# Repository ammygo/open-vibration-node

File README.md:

# Open Vibration Node

An open hardware and open firmware vibration sensing node for industrial condition
monitoring — analysing vibration **on the device** and reporting results over LoRaWAN to a
gateway you run yourself, with no mandatory cloud service.

> **Status: sensor board verified, radio path not yet exercised.** The second-generation
> sensor board has been manufactured and verified on the bench — the sensor identifies
> correctly, gravity and impact-response tests pass, and the noise floor sits at ~18 mg RMS
> across the full 6.3 kHz bandwidth on a bench ([measurements](docs/measurements.md)). The RAK3112 module has so far served only as the
> host MCU for those tests; the SX1262 radio has not yet been brought up. Mechanical
> integration and the signal-processing firmware are the current work.

*The two 28 mm boards that make up a node — sensor board and radio board, both sides.
More photographs: [docs/images](docs/images/).*

## Why this project exists

Predictive maintenance works: measuring vibration on motors, bearings, pumps and fans
reveals developing faults weeks or months before they cause a breakdown. The techniques
are well documented in engineering literature, and the sensors cost a few euros.

Access to them is not open, though. Commercial condition-monitoring systems are closed
end to end — proprietary sensors, proprietary gateways, and a vendor cloud that must stay
reachable and paid for, or the equipment stops being monitored. Prices start in the
hundreds of euros per measurement point, which puts continuous monitoring out of reach for
small manufacturers, municipal utilities, water pumping stations and building services —
exactly the operators who can least afford an unplanned failure.

Open vibration-monitoring projects do exist. The ones I have found stop at a development
board on a desk, depend on a vendor cloud, or use accelerometers limited to a few hundred
hertz — which rules out the 1–6 kHz region where bearing faults first appear. What is
missing is a node that combines the bandwidth needed for real diagnostics with local-first
operation and documentation good enough to rebuild it. This project aims to be that node.

## How this compares with existing work

| Approach | Usable bandwidth | Power / connectivity | Openness |
|---|---|---|---|
| Commercial condition-monitoring systems | Full (piezo-based) | Battery or wired; vendor cloud mandatory | Closed end to end; per-point pricing plus subscription |
| Open builds on consumer MEMS (ADXL345 / LIS3DH class) | ~200–800 Hz | Battery; various | Open, but physically blind to the 1–6 kHz bearing-fault region |
| Wired piezo + DAQ setups | Full | Mains power and cabling per point | Mixed; cabling dominates per-point cost |
| **This project** | **DC–6.3 kHz (IIS3DWB)** | **Battery + LoRa; local-first, no mandatory cloud** | **Open: hardware, firmware, docs, production files** |

Open lab-instrument projects — open microscopes, open test equipment — have already shown
that *laboratory-grade but open and rebuildable* is a workable model. This project applies
that model to industrial vibration monitoring.

## Design goals

These are the goals the design is being built towards, not a description of what already
works — see the status above.

- **Analysis on the device.** FFT and envelope processing run on the node's MCU. Only
  results leave the device — a compact payload of dominant frequencies, amplitudes, RMS
  and temperature (target: under 24 bytes), not raw waveforms. This is what makes
  battery-powered operation over a low-bandwidth radio possible at all.
- **Local-first.** LoRaWAN with a self-hosted [ChirpStack](https://www.chirpstack.io/)
  network server: the reference gateway is a Raspberry Pi 5 with an SX1302 eight-channel
  concentrator, and everything from radio to database runs on hardware the operator owns.
  No account, no vendor cloud, no remote kill switch. Cloud services are optional, never
  required.
- **Auditable and reproducible.** Schematics, bill of materials, firmware source and
  enclosure models under free licences, with build documentation detailed enough to
  reproduce a working node.
- **Long field life.** Multi-year operation on a primary lithium cell. Sealed enclosure
  for industrial and outdoor use.
- **Secure by design.** Per-device keys, signed firmware updates and a published software
  bill of materials, so that nodes remain maintainable under the EU Cyber Resilience Act
  rather than becoming unsupported hardware.

## Hardware

| Block | Part | Key figures |
|---|---|---|
| Accelerometer | STMicroelectronics **IIS3DWB** | DC–6.3 kHz flat bandwidth, 26.667 kHz ODR, 75 µg/√Hz noise density, ±2/4/8/16 g, SPI, −40…+105 °C, integrated temperature sensor |
| MCU + radio | RAK Wireless **RAK3112** | ESP32-S3 + Semtech SX1262 in one certified module (LoRa 868 MHz, WiFi, BLE), 23×15 mm |
| Power | Diodes **AP2112K-3.3** LDO | 600 mA, SOT-23-5 (LCSC C51118) |

### Why these parts

**IIS3DWB.** Bearing and mechanical fault signatures live in the 1–6 kHz region, while
ordinary MEMS accelerometers (ADXL345, LIS3DH and similar) are limited to 200–800 Hz —
they physically cannot see what matters. The IIS3DWB gives a flat 6.3 kHz bandwidth at
75 µg/√Hz noise in a single 2.5 × 3.0 mm package, so diagnostics that previously required
a piezoelectric accelerometer with an external conditioner now fit in a 28 mm node running
from a battery.

**RAK3112.** The ESP32-S3 has enough compute to run the FFT locally, which is the whole
premise of the design: the node transmits a spectral summary rather than raw waveforms,
which is what makes both the battery budget and the LoRa duty cycle work. Combining it
with the SX1262 in one certified module means a single component instead of MCU plus radio
plus RF matching, and no antenna network to design. The trade-off is board area in
exchange for reproducibility and a simpler certification path — a deliberate choice for a
project that others are meant to be able to rebuild.

*Everything that goes into one node: the two boards, primary cell, energy buffer,
antennas, printed housing and the aluminium mounting pad.*

### Board architecture

Two 28 mm round boards with the battery between them, joined by seven wires:

- **Sensor board** — IIS3DWB on the bottom layer, facing the measured surface, with
  decoupling capacitors and a CS pull-up.
- **Radio board** — RAK3112 on the top layer (antenna facing away from metal), LDO and
  power components underneath.

Inter-board signals: `GND`, `3V3`, `SPI_CS`, `SPI_SCK`, `SPI_MISO`, `SPI_MOSI`, `INT1`.
Pad order is identical on both boards, so the wires run straight across without crossing.

Placing the accelerometer on the bottom layer is deliberate — it shortens the mechanical
path between the measured surface and the sensing element, which matters far more for
signal fidelity than any amount of filtering afterwards.

### Two data paths

A node normally sends only a spectral summary — a payload of a couple of dozen bytes,
which is what makes years of battery life on a low-bandwidth radio possible at all. That
summary is enough to trend a machine's condition, but not to investigate a fault in detail.

So the node keeps a second path. The RAK3112 carries 8 MB of PSRAM, enough to hold about
50 seconds of the full 26.667 kHz three-axis stream. When something in the trend needs
looking at, an engineer standing next to the machine can trigger a capture and pull the
raw recording off over WiFi, straight to a laptop — no cloud and no gateway involved.
This path works on the bench as of September 2026: a downlink command makes the node record
32768 samples per axis (1.23 s — the PSRAM allows about 50 s; 1.23 s is the current capture
length) from the sensor FIFO into PSRAM and post them over WiFi to the collector (the local
server described above; a laptop also works), which it locates by mDNS.

This is deliberately **on demand** rather than continuous: streaming raw data would end the
battery budget within days. Routine monitoring stays cheap; full detail is available when
it is actually needed.

## Repository layout

| Path | Contents |
|---|---|
| `firmware/tests/` | Bench verification sketches — sensor identification and acquisition |
| `firmware/bench-node/` | Interim point-to-point LoRa node and bench receiver — FIFO acquisition, ISO 10816 velocity RMS, health reporting, raw capture over WiFi |
| `docs/` | Measurements, payload specification draft, build notes |
| `enclosure/` | Mounting pad and housing — CAD sources with open-format exports |
| `tools/` | Design-check utilities: a mirrored-footprint checker and the velocity-RMS filter validation script |
| `hardware/` | KiCad boards plus gerbers, BOM and pick-and-place files for both boards |

## Licences

- Firmware and software: [MIT](LICENSE)
- Hardware design files: CERN-OHL-W-2.0 (see `hardware/LICENSE.txt`)
- Documentation: CC-BY-SA-4.0

## Roadmap

Timing is indicative and assumes part-time development; with project funding it compresses.

1. ~~Sensor board validated on hardware~~ — done, August 2026 ([measurements](docs/measurements.md))
2. ~~Radio bring-up: SX1262 transmit and receive path~~ — done, September 2026: point-to-point
   LoRa link (869.525 MHz, SF7) in both directions, downlink-configurable cadence within the
   duty-cycle budget, on-demand raw capture over WiFi; velocity RMS in the ISO 10816 band
   validated ([measurements](docs/measurements.md#velocity-rms-in-the-iso-10816-band-added-2-september-2026)).
   The interim link terminates in a USB LoRa receiver on the collector (the local server
   described under *Local-first*); roadmap item 4 replaces it with the SX1302 LoRaWAN gateway
   and ChirpStack.
3. Mechanical integration: sensor coupling, sealing, field-ready housing (pad and housing
   models [published](enclosure/); sealing details in progress) — winter 2026/27
4. On-device FFT and envelope processing, LoRaWAN uplink with a versioned payload format
   ([draft specification](docs/payload-spec.md)) — spring 2027. *Interim: FFT, envelope and
   waterfall spectra are computed on the collector from FIFO captures; each packet already
   carries band-limited velocity RMS, crest factor and a sensor-health flag
   ([status](docs/payload-spec.md#bench-protocol-status-2-september-2026)).*
5. Characterisation against a reference accelerometer on a shaker — spring/summer 2027
6. Field deployment on real rotating equipment, with published measurement data — second
   half of 2027
7. Documented reproducible build — someone else assembles a node from this repository —
   late 2027

## About

Built by Laurynas Misiūnas, an electronics engineer in Klaipėda district, Lithuania, with
six years of industrial experience deploying edge AI vision systems and embedded
controllers on production lines. Developed with the support of the Klaipėda Science and
Technology Park (KMTP) innovation support programme.

Contributions, review and questions are welcome — see [CONTRIBUTING.md](CONTRIBUTING.md) or open an issue.

## Transparency: use of generative AI

Engineering decisions, architecture and project direction in this repository are made by
the author. Documentation and English-language texts are drafted with the assistance of a
large language model (Anthropic Claude) and reviewed, corrected and approved by the author
before publication. Commits with LLM-assisted content carry a `Co-Authored-By: Claude`
trailer. Details in [TRANSPARENCY.md](TRANSPARENCY.md).

No firmware, hardware design files or measurement data will be presented as project
deliverables without human authorship and verification.

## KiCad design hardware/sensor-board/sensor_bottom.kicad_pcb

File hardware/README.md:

# Hardware

Two 28 mm round boards, joined by seven wires with the battery between them.

Licence: CERN-OHL-W-2.0 — see [LICENSE.txt](LICENSE.txt).

| Path | Board | Contents |
|---|---|---|
| `sensor-board/` | IIS3DWB accelerometer, bottom layer | KiCad board, gerbers, BOM, pick-and-place |
| `radio-board/` | RAK3112 module (ESP32-S3 + SX1262), LDO | KiCad board, gerbers, BOM, CPL, pick-and-place |

The `production/` files under each board are the sets actually sent for fabrication and
assembly — not idealised exports. Boards from these files have been manufactured and the
sensor board verified on the bench ([measurements](../docs/measurements.md)).

### What the KiCad sources are and are not

**The gerbers are the authoritative artifact** — they are what was manufactured. The KiCad
files are the design sources behind them, and on both boards they differ from the gerbers
in ways worth knowing before you rebuild:

- **Sensor board** — fully routed, but one CS track and its via sit about 0.1 mm from
  where the manufactured gerbers place them. The final clearance fix was applied in the
  export tool rather than back-annotated to KiCad. Electrically identical; regenerating
  gerbers from KiCad will not produce a byte-identical set.
- **Radio board** — carries **placement and netlist only, with no routing**. The routing
  was done in the export tool and exists solely in the gerbers. Opening this file will
  show an unrouted board; that is the actual state of the source, not a damaged file.

If you intend to modify either design, start from the gerbers for what was built and treat
the KiCad files as the placement reference.

*Sensor board (bottom row) and radio board (top row), both sides. The accelerometer sits
on the underside of the sensor board; the RAK3112 module on the top of the radio board.*

## Inter-board wiring

`GND`, `3V3`, `SPI_CS`, `SPI_SCK`, `SPI_MISO`, `SPI_MOSI`, `INT1`.

Pad order is identical on both boards, so the wires run straight across without crossing.

## Layout constraints worth knowing

Two requirements pull against each other on a 28 mm board, and the layout is the
compromise between them:

- The accelerometer needs a **short, stiff mechanical path** to the mounting surface,
  which is why it sits on the bottom layer facing the measured surface rather than on top.
- The radio needs a **clean ground plane and antenna keep-out**, which is why the module
  sits on the top layer with the antenna facing away from the mounted metal.

Splitting these onto two boards resolves the conflict; the cost is the seven-wire harness
and the assembly step that goes with it.

## Before you reorder these boards

Run [`../tools/check_handedness.py`](../tools/README.md) against the sensor board. A
mirrored bottom-layer footprint passes design rule checking and fabricator review and
still cannot be assembled — that mistake cost three revisions here.

## Bill of materials

The BOM files carry LCSC part numbers where the boards were assembled with them, so the
component selection can be reproduced directly. Prices, suppliers and order references are
deliberately not included.

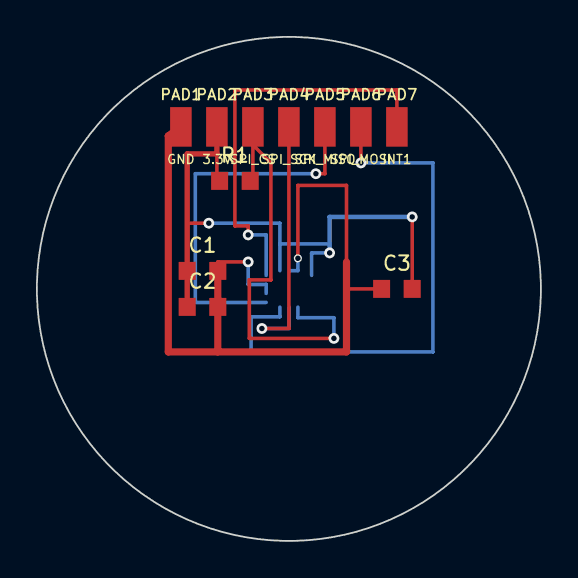
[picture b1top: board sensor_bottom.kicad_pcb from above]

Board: 2 copper layers, 28.0 x 28.0 mm, 12 parts (1 on the bottom side), 7 nets.

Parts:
C1, C3: 100nF; C_0603_1608Metric
C2: 1uF; C_0603_1608Metric
PAD1: GND; PinHeader_1x01_P2.00mm_Vertical
PAD2: 3.3V; PinHeader_1x01_P2.00mm_Vertical
PAD3: SPI_CS; PinHeader_1x01_P2.00mm_Vertical
PAD4: SPI_SCK; PinHeader_1x01_P2.00mm_Vertical
PAD5: SPI_MISO; PinHeader_1x01_P2.00mm_Vertical
PAD6: SPI_MOSI; PinHeader_1x01_P2.00mm_Vertical
PAD7: INT1; PinHeader_1x01_P2.00mm_Vertical
R1: 10k; R_0603_1608Metric
U1: IIS3DWB; LGA-14_3x2.5mm_P0.5mm

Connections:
3.3V: C1.1, C2.1, C3.2, PAD2.2, R1.1, U1.5, U1.8
GND: C1.2, C2.2, C3.1, PAD1.1, U1.2, U1.3, U1.6, U1.7
INT1: PAD7.7, U1.4
SPI_CS: PAD3.3, R1.2, U1.12
SPI_MISO: PAD5.5, U1.1
SPI_MOSI: PAD6.6, U1.14
SPI_SCK: PAD4.4, U1.13

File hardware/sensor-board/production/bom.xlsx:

No. | Quantity | Comment | Designator | Footprint | Value | Manufacturer Part | Manufacturer | Supplier Part | Supplier
1 | 2 | 100nF | C1,C3 | Capacitor_SMD:C_0603_1608Metric
2 | 1 | 1uF | C2 | Capacitor_SMD:C_0603_1608Metric
3 | 1 | GND | PAD1 | Connector_PinHeader_2.00mm:PinHeader_1x01_P2.00mm_Vertical
4 | 1 | 3.3V | PAD2 | Connector_PinHeader_2.00mm:PinHeader_1x01_P2.00mm_Vertical
5 | 1 | SPI_CS | PAD3 | Connector_PinHeader_2.00mm:PinHeader_1x01_P2.00mm_Vertical
6 | 1 | SPI_SCK | PAD4 | Connector_PinHeader_2.00mm:PinHeader_1x01_P2.00mm_Vertical
7 | 1 | SPI_MISO | PAD5 | Connector_PinHeader_2.00mm:PinHeader_1x01_P2.00mm_Vertical
8 | 1 | SPI_MOSI | PAD6 | Connector_PinHeader_2.00mm:PinHeader_1x01_P2.00mm_Vertical
9 | 1 | INT1 | PAD7 | Connector_PinHeader_2.00mm:PinHeader_1x01_P2.00mm_Vertical
10 | 1 | 10k | R1 | Resistor_SMD:R_0603_1608Metric
11 | 1 | IIS3DWB | U1 | Package_LGA:LGA-14_3x2.5mm_P0.5mm

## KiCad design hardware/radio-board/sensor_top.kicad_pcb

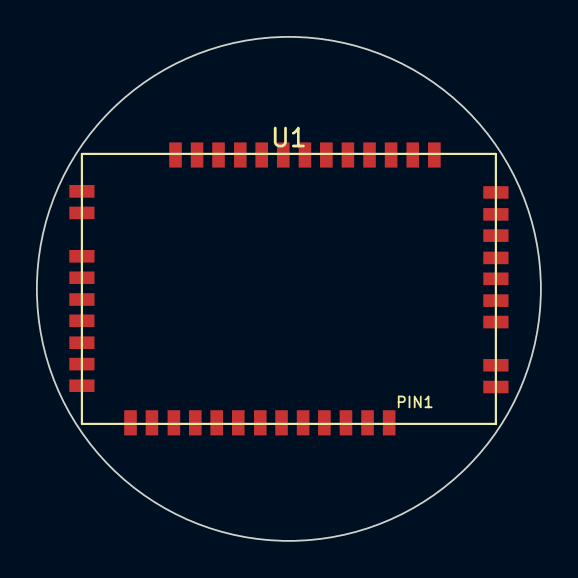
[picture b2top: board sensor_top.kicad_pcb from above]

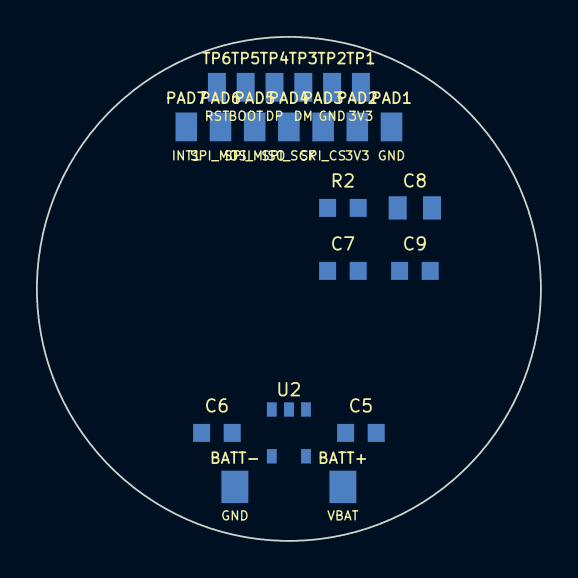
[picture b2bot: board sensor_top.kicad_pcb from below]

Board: 2 copper layers, 28.0 x 28.0 mm, 23 parts (22 on the bottom side), 12 nets, no tracks yet.

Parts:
BATT+: VBAT; PinHeader_1x01_P2.54mm_Vertical
BATT-: GND; PinHeader_1x01_P2.54mm_Vertical
C5, C6, C7: 1uF; C_0603_1608Metric
C8: 10uF; C_0805_2012Metric
C9: 100nF; C_0603_1608Metric
PAD1: GND; PinHeader_1x01_P2.00mm_Vertical
PAD2: 3V3; PinHeader_1x01_P2.00mm_Vertical
PAD3: SPI_CS; PinHeader_1x01_P2.00mm_Vertical
PAD4: SPI_SCK; PinHeader_1x01_P2.00mm_Vertical
PAD5: SPI_MISO; PinHeader_1x01_P2.00mm_Vertical
PAD6: SPI_MOSI; PinHeader_1x01_P2.00mm_Vertical
PAD7: INT1; PinHeader_1x01_P2.00mm_Vertical
R2: 10k; R_0603_1608Metric
TP1: 3V3; PinHeader_1x01_P2.00mm_Vertical
TP2: GND; PinHeader_1x01_P2.00mm_Vertical
TP3: DM; PinHeader_1x01_P2.00mm_Vertical
TP4: DP; PinHeader_1x01_P2.00mm_Vertical
TP5: BOOT; PinHeader_1x01_P2.00mm_Vertical
TP6: RST; PinHeader_1x01_P2.00mm_Vertical
U1: RAK3112
U2: AP2112K-3.3; SOT-23-5

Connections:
3V3: C6.1, C8.1, C9.1, PAD2.1, R2.1, TP1.1, U1.20, U1.21, U2.5
BOOT: TP5.1, U1.24
GND: BATT-.1, C5.2, C6.2, C7.2, C8.2, C9.2, PAD1.1, TP2.1, U1.14, U1.16, U1.22, U1.35, U1.36, U1.38, U1.42, U2.2
INT1: PAD7.1, U1.34
RESET: C7.1, R2.2, TP6.1, U1.17
SPI_CS: PAD3.1, U1.32
SPI_MISO: PAD5.1, U1.30
SPI_MOSI: PAD6.1, U1.31
SPI_SCK: PAD4.1, U1.33
USB_DM: TP3.1, U1.2
USB_DP: TP4.1, U1.3
VBAT: BATT+.1, C5.1, U2.1, U2.3
